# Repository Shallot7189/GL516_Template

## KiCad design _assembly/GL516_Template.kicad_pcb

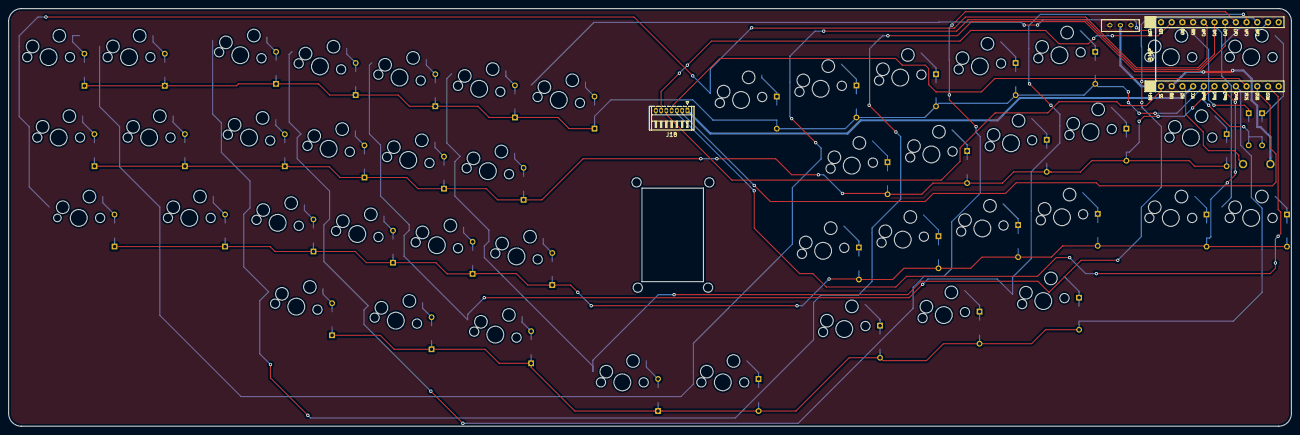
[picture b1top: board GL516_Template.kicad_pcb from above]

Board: 2 copper layers, 304.8 x 99.2 mm, 94 parts (0 on the bottom side), 65 nets.

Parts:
D1, D2, D3, D4, D5, D6, D7, D8, D9, D10, D11, D12, D13, D14, D15, D16, D17, D18, D19, D20, D21, D22, D23, D24, D25, D26, D27, D28, D29, D30, D31, D32, D33, D34, D35, D36, D37, D38, D39, D40, D41, D42, D43, D44, D45: D; Diode_TH_SMD
J1: Conn_01x02; Battery_XH2.5_GL
J18: Conn_01x07; Hirose_DF13-07P-1.25DS_1x07_P1.25mm_Horizontal
SW1, SW2, SW3, SW4, SW5, SW6, SW7, SW9, SW10, SW11, SW12, SW13, SW15, SW16, SW17, SW18, SW19, SW24, SW25, SW26, SW27, SW28, SW31, SW32, SW33, SW34, SW35, SW36, SW37, SW38, SW39, SW40, SW41: SW_PUSH; CherryMX_Hotswap_1.0u
SW8, SW20, SW21, SW22, SW23, SW42, SW43, SW44, SW45: SW_PUSH; CherryMX_Hotswap_1.25u
SW14: SW_PUSH; CherryMX_Hotswap_1.75u
SW29, SW30: SW_PUSH; CherryMX_Hotswap_1.0u_Small1
SW81: SW_PUSH; ResetSW
U1: BLEMicroPro; Micon_BMP_GL

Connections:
Bat+: J1.1, U1.25
Col0: SW1.1, SW8.1, SW14.1, SW24.1, U1.5
Col1: SW2.1, SW9.1, SW15.1, SW25.1, SW31.1, SW36.1, SW42.1, U1.6
Col2: SW3.1, SW10.1, SW16.1, SW20.1, SW26.1, SW32.1, SW37.1, SW43.1, U1.7
Col3: SW4.1, SW11.1, SW17.1, SW21.1, SW27.1, SW33.1, SW38.1, SW44.1, U1.8
Col4: SW5.1, SW12.1, SW18.1, SW22.1, SW28.1, SW34.1, SW39.1, SW45.1, U1.9
Col5: SW6.1, SW13.1, SW19.1, SW23.1, SW29.1, SW35.1, SW40.1, U1.10
Col6: SW7.1, SW30.1, SW41.1, U1.11
GND: J1.2, J18.7, SW81.2, U1.3, U1.4, U1.23, U1.26
MISO: J18.2, U1.15
MOSI: J18.3, U1.14
MOTION: J18.6, U1.2
unnamed: D1.2, SW1.2
unnamed: D2.2, SW2.2
unnamed: D3.2, SW3.2
unnamed: D4.2, SW4.2
unnamed: D5.2, SW5.2
unnamed: D6.2, SW6.2
unnamed: D7.2, SW7.2
unnamed: D8.2, SW8.2
unnamed: D9.2, SW9.2
unnamed: D10.2, SW10.2
unnamed: D11.2, SW11.2
unnamed: D12.2, SW12.2
unnamed: D13.2, SW13.2
unnamed: D14.2, SW14.2
unnamed: D15.2, SW15.2
unnamed: D16.2, SW16.2
unnamed: D17.2, SW17.2
unnamed: D18.2, SW18.2
unnamed: D19.2, SW19.2
unnamed: D20.2, SW20.2
unnamed: D21.2, SW21.2
unnamed: D22.2, SW22.2
unnamed: D23.2, SW23.2
unnamed: D24.1, SW24.2
unnamed: D25.1, SW25.2
unnamed: D26.1, SW26.2
unnamed: D27.1, SW27.2
unnamed: D28.1, SW28.2
unnamed: D29.1, SW29.2
unnamed: D30.1, SW30.2
unnamed: D31.1, SW31.2
unnamed: D32.1, SW32.2
unnamed: D33.1, SW33.2
unnamed: D34.1, SW34.2
unnamed: D35.1, SW35.2
unnamed: D36.1, SW36.2
unnamed: D37.1, SW37.2
unnamed: D38.1, SW38.2
unnamed: D39.1, SW39.2
unnamed: D40.1, SW40.2
unnamed: D41.1, SW41.2
unnamed: D42.1, SW42.2
unnamed: D43.1, SW43.2
unnamed: D44.1, SW44.2
unnamed: D45.1, SW45.2
Reset: SW81.1, U1.22
Row0: D1.1, D2.1, D3.1, D4.1, D5.1, D6.1, D7.1, D24.2, D25.2, D26.2, D27.2, D28.2, D29.2, D30.2, U1.20
Row1: D8.1, D9.1, D10.1, D11.1, D12.1, D13.1, D31.2, D32.2, D33.2, D34.2, D35.2, U1.19
Row2: D14.1, D15.1, D16.1, D17.1, D18.1, D19.1, D36.2, D37.2, D38.2, D39.2, D40.2, D41.2, U1.18
Row3: D20.1, D21.1, D22.1, D23.1, D42.2, D43.2, D44.2, D45.2, U1.17
SCLK: J18.4, U1.16
SS: J18.5, U1.24
VCC: J18.1, U1.21

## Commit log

2021-07-07 Alice with TrackBall TopPlate Create
2021-07-19 外形線をオリジナルに合わせて変更
2021-07-26 トラックボール穴位置調整
2021-07-26 フォルダ構成変更、PCB作成中
2021-07-27 PCB作成
2021-07-28 トッププレート調整中
2021-07-28 発注done
